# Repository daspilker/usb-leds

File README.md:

USB LEDs
========

[Eagle CAD](http://www.cadsoftusa.com/) design files for a USB status LED circuit.

See http://www.daniel-spilker.com/blog/2012/11/17/usb-leds-for-media-center-pc/ for details.

Part List
---------

<table>
    <tr>
        <th>Position</td>
        <th>Description</td>
        <th>Digi-Key Part Number</td>
    </tr>
    <tr>
	<td>CON1, CON2, CON3</td>
        <td>CONN HEADER .100 SINGL STR 36POS</td>
	<td>S1011E-36-ND</td>
    </tr>
    <tr>
	<td>CON4</td>
	<td>CONN FEMALE 4POS .100" R/A GOLD</td>
	<td>S5479-ND</td>
    </tr>
    <tr>
	<td>C1</td>
	<td>CAP TANT 4.7UF 6.3V 20% SMD</td>
	<td>511-1443-1-ND</td>
    </tr>
    <tr>
	<td>C2, C3</td>
	<td>CAP CERM .1UF 10% 50V X7R 0805</td>
	<td>478-1395-1-ND</td>
    </tr>
    <tr>
	<td>FB1</td>
	<td>FERRITE 1.5A 40 OHM 0805 SMD</td>
	<td>240-2389-1-ND</td>
    </tr>
    <tr>
	<td>IC1</td>
	<td>IC USB FS SERIAL UART 28-SSOP</td>
	<td>768-1007-1-ND</td>
    </tr>
    <tr>
	<td>R1, R2, R3</td>
	<td>RES 680 OHM 1/8W 5% 0805 SMD</td>
	<td>P680ACT-ND</td>
    </tr>
    <tr>
	<td>R4</td>
	<td>RES 10.0K OHM 1/8W 1% 0805 SMD</td>
	<td>RHM10.0KCCT-ND</td>
    </tr>
    <tr>
	<td>R5, R6, R7</td>
	<td>TRIMMER 5K OHM 0.25W SMD</td>
	<td>3314J-502ECT-ND</td>
    </tr>
</table>

License
-------

Copyright (c) 2012, Daniel A. Spilker

This work is licensed under a Creative Commons Attribution-ShareAlike 3.0 Germany License. To view a copy of this license, visit http://creativecommons.org/licenses/by-sa/3.0/de/deed.en.

http://daniel-spilker.com/

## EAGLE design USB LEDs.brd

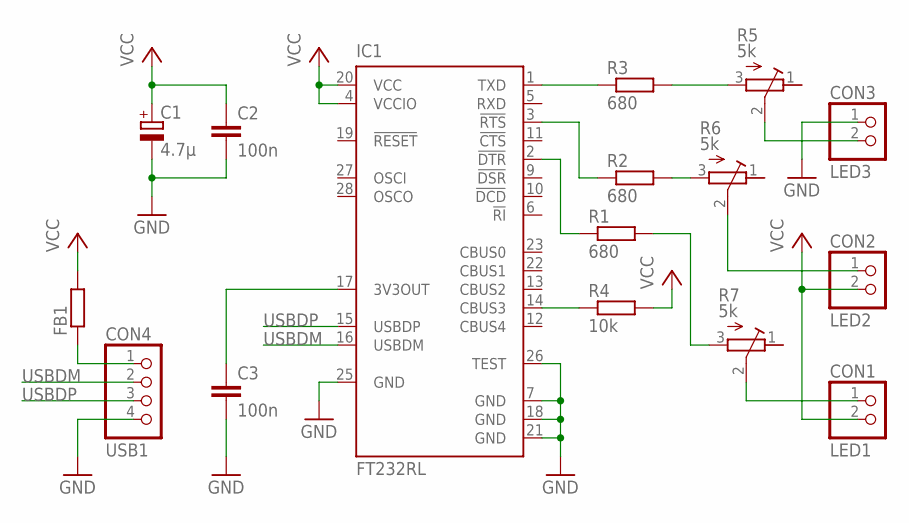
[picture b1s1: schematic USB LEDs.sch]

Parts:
C1: 4.7µ; R/2012-12R
C2, C3: 100n; C0805
CON1: LED1; 1X02
CON2: LED2; 1X02
CON3: LED3; 1X02
CON4: USB1; 1X04
FB1: R-EU_R0805; R0805
IC1: FT232RL; SSOP28
R1, R2, R3: 680; R0805
R4: 10k; R0805
R5, R6, R7: 5k; RTRIM3314J

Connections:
GND: C1.-, C2.2, C3.2, CON3.1, CON4.4, IC1.7 (GND), IC1.18 (GND), IC1.21 (GND), IC1.25 (GND), IC1.26 (TEST)
unnamed: C3.1, IC1.17 (3V3OUT)
unnamed: CON3.2, R5.2 (S)
unnamed: R3.2, R5.3 (A)
unnamed: CON4.1, FB1.1
unnamed: IC1.2 (!DTR), R1.1
unnamed: IC1.3 (!RTS), R2.1
unnamed: IC1.14 (CBUS3), R4.1
unnamed: CON2.1, R6.2 (S)
unnamed: R1.2, R7.3 (A)
unnamed: CON1.1, R7.2 (S)
unnamed: R2.2, R6.3 (A)
TXD: IC1.1 (TXD), R3.1
USBDM: CON4.2, IC1.16 (USBDM)
USBDP: CON4.3, IC1.15 (USBDP)
VCC: C1.+, C2.1, CON1.2, CON2.2, FB1.2, IC1.4 (VCCIO), IC1.20 (VCC), R4.2

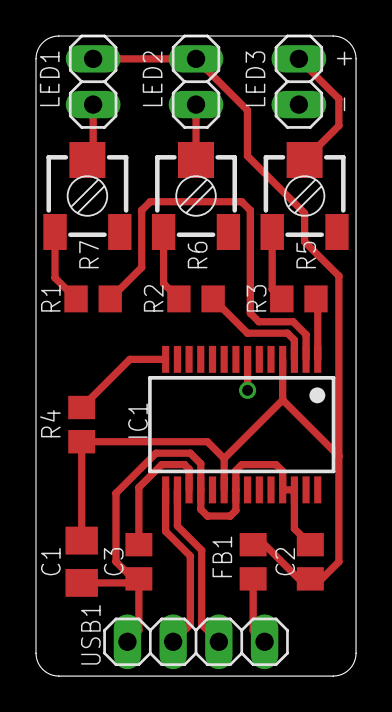
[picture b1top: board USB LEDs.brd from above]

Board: 2 copper layers, 17.8 x 35.6 mm, 16 parts (0 on the bottom side), 16 nets.

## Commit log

2012-11-17 README is in markdown format
2012-11-17 README in textile format
2012-11-17 added images to README
